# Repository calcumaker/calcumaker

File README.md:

# Calcumaker 16

> Repo: `calcumaker` · Product: **Calcumaker 16** (see [`NAMING.md`](NAMING.md))

A wide-format, full-size **Cherry MX** **programmer's / technical RPN
calculator**. It carries the HP-16C tradition — hexadecimal / octal / binary /
decimal entry, bitwise operators, and selectable word sizes — and extends it far
past what any single Voyager could do, with **arbitrary-precision** math: **GNU
MP** for big integers, **MPFR** for correctly-rounded floating-point and
transcendentals, and **MPC** for complex numbers. The 16C is the grounding
default (a faithful programmer's machine — `√-1` is `Error 0`, just like the
real one); switchable **personalities** (16C / 15C / SCI / FIN) and a SETUP menu
turn on the scientific and complex features on top. The top of the RPN stack is
shown live on a **multi-row 7-segment display** (2–3 rows) that mounts on its
**own angled PCB**. Battery + USB-C powered; a low-power STM32 keeps it alive
between keystrokes.

> Real keyswitches, a real stack you can see, and answers that are correct to as
> many digits as you ask for.

## Features

- **Programmer's RPN core (HP-16C lineage):** HEX/DEC/OCT/BIN modes, bitwise and
  shift/rotate ops, selectable word size, two's-complement / unsigned / one's-
  complement integer modes.
- **Arbitrary precision (single math path — no fallback):**
  - **GNU MP (libgmp)** — unbounded integers (huge hex/decimal, exact bitwise).
  - **MPFR (libmpfr)** — correctly-rounded floating point + transcendentals
    (sin/cos/exp/ln/…) at user-selectable precision.
  - **MPC (libmpc)** — arbitrary-precision **complex numbers** (HP-42S/15C model:
    one stack object, rectangular `a+bi` or polar `r∠θ`, complex-aware functions,
    CPXRES auto-promotion so `√-4 → 2i`). Off on the 16C, on for the scientific
    personalities and toggleable in SETUP.
  - Packaged as the **`calcumaker-core`** library (`no_std`) over our own
    **`gmp-mpfr-nostd`** FFI bindings — host-testable and runnable today
    (`cargo test`, `cargo run --example repl`).
- **Switchable personalities:** **16C** (programmer, the grounding default),
  **15C** (advanced scientific — the one that natively had complex), **SCI**
  (general scientific), **FIN** (HP-12C-style financial) — one keyboard, chosen
  in SETUP, each just a keymap + defaults over the same superset engine.
- **Field updates over USB-C:** flash new firmware with `dfu-util` via the STM32
  ROM DFU bootloader (`make dfu`) — no ST-Link needed; BOOT0 is the backup.
- **Host emulator:** `calcumaker-emu` runs the whole device UI — keymap, f/g
  shifts, digit entry, the multi-row 7-seg display rendered from the real
  TM1640 segment bytes — on a standard terminal (`cargo run`).
- **Visible RPN stack:** multi-row 7-segment display (2–3 rows) shows the top of
  the stack at once.
- **Split design:** the display lives on its **own PCB** that angles upward;
  only power, the display serial bus, and optional aux-display I²C cross the FFC
  to the MCU board — which keeps wiring simple.
- **Full-size Cherry MX keyswitches:** a wide, tactile, technical-use keypad.
- **Battery + USB-C:** 1S Li-ion with USB-C charging + buck-boost rail; aggressive
  sleep between keypresses for long runtime.
- **Rust firmware:** `no_std` main loop on the **STM32U575RGT6** (Cortex-M33,
  1 MB / 768 KB, ULP — see `DESIGN.md`).

## Hardware Stack

Calcumaker 16 is a three-board KiCad 10 design:

- **`calcumaker-mcu`** is the bottom brain/PSU board: STM32U575, USB-C power and
  charging, the 3V3 rail, the gated 5V display rail, SWD, clocking, the display
  FFC connector, and the keyboard mezzanine.
- **`calcumaker-keyboard`** is the top/front-panel board: 49 Cherry MX keys (a 2U ENTER),
  per-key diodes, annunciator LEDs, and a small STM32G0 keyboard scanner that
  reports key events to the U575 instead of routing the raw matrix across the
  stack.
- **`calcumaker-display`** is the angled display board: three repeated 16-digit
  7-segment rows driven by TM1640s, plus the display FFC and optional aux OLED
  socket.

The schematics are generated from per-board manifests under `hardware/scripts/`
and then placed/wired in KiCad. The display board uses a fully wired
multi-channel row sheet; the MCU and keyboard boards carry the generated sheet
structure plus on-canvas wiring notes. See [`hardware/README.md`](hardware/README.md)
and [`DESIGN.md`](DESIGN.md) for the current hardware source of truth.

## Architecture

```
   DISPLAY BOARD (calcumaker-display) — angled, cabled to the MCU board
   ┌──────────────────────────────────────────────────┐
   │  7-segment RPN stack: 3 rows × 16 digits (2–3 on) │
   │   48× FJ5161AH 0.56" single-digit CC (THT)        │
   │   3× TM1640 driver (1 per row, 2-wire bus)        │
   └──────────────────────────────────────────────────┘
       │ 12-position 0.5mm FFC: +5V, GND, CLK + DIN×3
       │ (5V logic) + 3V3/I²C for the aux OLED — cables down to the MCU board
       ╧
   KEYBOARD BOARD (calcumaker-keyboard) — TOP of stack, keys face up
   ┌──────────────────────────────────────────────────┐
   │  full-size Cherry MX key matrix (+ per-key diode) │
   │  STM32G0 scanner + annunciator LEDs (f g C G lo-b)│
   └──────────────────────┬┬──────────────────────────┘
     low-profile Hirose DF40 mezzanine (0.4mm, 1.5mm stack) + standoffs
        ││  I²C + UART + KB_IRQ (wake) + 3V3/GND  (matrix stays on the G0)
   MCU BOARD (calcumaker-mcu) — BOTTOM of stack
   ┌──────────────────────┴┴──────────────────────────┐
   │  EN-gated 5V boost ──► display │ 74HCT125 (3V3→5V)│
   │   ┌───────────────────────────────────────────┐   │  USB-C ── console /
   │   │ STM32U575RGT6 (Cortex-M33, 1MB/768KB, ULP) │   │          provisioning
   │   │  Rust no_std main loop (embassy)           │   │
   │   │   calcumaker-core: RPN engine              │   │
   │   │        └ GMP + MPFR  (single path)         │   │
   │   │   heap: embedded-alloc (TLSF)              │   │
   │   └────────────────────────────────────────────┘   │
   └───────┬───────────────────────────────────────────┘
           │ VSYS
   1S Li-ion ── USB-C charger ── load-share ── VSYS ──┬── buck-boost → 3V3 (MCU, ULP)
                                                      └── 5V boost (EN-gated) → display
```

## Firmware Stack

The firmware is deliberately split so there is one calculator and multiple thin
I/O bindings around it:

```
   host terminal                         STM32U575 firmware
   ┌─────────────────────┐               ┌─────────────────────┐
   │ calcumaker-emu      │               │ calcumaker-fw       │
   │ crossterm UI        │               │ no_std / embassy    │
   │ host keys + ASCII   │               │ keyboard link +     │
   │ 7-seg rendering     │               │ TM1640 bus + heap   │
   └──────────┬──────────┘               └──────────┬──────────┘
              │                                     │
              └──────────────┬──────────────────────┘
                             │
                    ┌────────▼────────┐
                    │ calcumaker-core │
                    │ Calc + App +    │
                    │ keys + seg7     │
                    └────────┬────────┘
                             │
                    ┌────────▼────────┐
                    │ gmp-mpfr-nostd  │
                    │ Integer + Float │
                    └────────┬────────┘
                             │
          host system GMP/MPFR or target cross-built GMP/MPFR
```

- **`gmp-mpfr-nostd`** is the math FFI layer: `no_std` + `alloc` wrappers for
  GMP integers and MPFR floats. On the host it links system/Homebrew GMP+MPFR;
  on the MCU it links the cross-built static libraries.
- **`calcumaker-core`** is the calculator: RPN stack, exact integer/programmer
  operations, MPFR real math, modes, keymap and f/g shift layers, entry editing,
  errors, and TM1640 7-segment byte generation. This crate is the single numeric
  path: no `rug`, no `std`, no pure-Rust fallback.
- **`calcumaker-emu`** runs the same `App` on a desktop terminal. It maps host
  keys to the physical matrix and renders the real segment bytes as 7-segment
  art, so scripted examples exercise the same key handling and display pipeline
  the device uses.
- **`calcumaker-fw`** is the U575 board binding: heap setup, power/display
  bring-up, keyboard event intake, and the TM1640 bus. The keyboard board's G0
  firmware owns matrix scan, debounce, wake/IRQ, and annunciator drive; the U575
  consumes `(row,col)` key events and feeds them to `calcumaker_core::App`.

Useful firmware entry points:

```sh
cd firmware/calcumaker-core
cargo test
cargo run --example repl

cd ../calcumaker-emu
cargo run
cargo run -- --press "2;3+"

cd ../..
firmware/scripts/build-gmp-mpfr-arm.sh
```

Host engine tests, the token REPL, and the terminal emulator work today against
the real GMP/MPFR libraries. The target GMP/MPFR build is cross-built and
link-verified; remaining firmware work is MCU/HAL bring-up, newlib/libm link
cleanup, heap routing for GMP allocations, and the keyboard-G0 firmware.

## Repository Structure

```
calcumaker/
├── hardware/                     # PCB design (KiCad 10) — split, three boards
│   ├── lib/                      # project-specific symbols/footprints/3D (shared)
│   │   ├── symbols/ footprints.pretty/ 3dmodels/
│   ├── calcumaker-mcu/           # MCU board (brain/PSU): MCU + PSU + clock + SWD + display-IF + keyboard mezzanine
│   │   ├── calcumaker-mcu.kicad_pro
│   │   ├── (root + mcu / clock / prog / psu / display_if / keyboard_if sub-sheets — generated)
│   │   ├── sym-lib-table · fp-lib-table
│   ├── calcumaker-keyboard/      # keyboard board (stacks above MCU): Cherry MX matrix + annunciators + MCU mezzanine
│   │   ├── calcumaker-keyboard.kicad_pro
│   │   ├── (root + keypad / annunc / main_if sub-sheets — generated)
│   │   ├── sym-lib-table · fp-lib-table
│   ├── calcumaker-display/       # display board (angled, cabled): 7-seg stack + driver + interconnect
│   │   ├── calcumaker-display.kicad_pro
│   │   ├── (root + display_row ×3 / interconnect / aux sub-sheets — generated)
│   │   ├── sym-lib-table · fp-lib-table
│   ├── scripts/                  # schgen engine + per-board manifests, check/render, JLCPCB
│   ├── Makefile                  # PROJECTS = calcumaker-mcu calcumaker-keyboard calcumaker-display
│   ├── LICENSE                   # CERN-OHL-S v2 (hardware)
│   ├── README.md
│   ├── sym-lib-table
│   └── fp-lib-table
├── firmware/
│   ├── gmp-mpfr-nostd/           # own no_std FFI to GMP/MPFR ("rug, but no_std")
│   ├── calcumaker-core/          # the CALCULATOR: engine + keymap + App + 7-seg
│   │   ├── src/                  #   lib, calc, value, format, keys, app, seg7
│   │   ├── tests/ · examples/repl.rs
│   │   └── Cargo.toml            #   single math path (no fallback)
│   ├── calcumaker-emu/           # HOST EMULATOR: the same App on a terminal
│   ├── calcumaker-fw/            # Rust no_std board binary (STM32U575 / embassy)
│   │   ├── Cargo.toml · .cargo/config.toml
│   │   ├── memory.x · build.rs · rust-toolchain.toml
│   │   └── src/                  #   main, keyboard input/link, display (TM1640 bus)
│   ├── scripts/                  # build-gmp-mpfr-arm.sh (cross-build for thumbv8m)
│   ├── common/                   # shared HAL/utilities
│   └── shared/                   # shared protocol/definitions
├── reference/                    # datasheets + dependency pointers
├── DESIGN.md                     # full hardware/firmware design + open questions
├── NAMING.md                     # product naming (Calcumaker 16)
└── LICENSE                       # AGPL-3.0 (firmware)
```

## Key Components

| Component | Part | Status |
|-----------|------|--------|
| MCU | STM32U575RGT6 (1MB/768KB, M33, ULP, LQFP-64) | ✅ selected — LCSC C5270980, JLCPCB Extended |
| Display | 3 rows × 16 digits: 3× TM1640 + 48× FJ5161AH 0.56" CC (THT) | ✅ LCSC C5337152 / C8093 |
| Keys | 5×10 grid, 49 full-size Cherry MX (2U double-height ENTER) + keyboard STM32G0 scanner | electrical/keymap decided; physical layout details still TBD |
| Display interconnect | 12-position 0.5mm FFC: +5V/GND, CLK + DIN×3, 3V3/I²C aux lines | selected in `DESIGN.md`; verify cable length/orientation at layout |
| Power | 1S Li-ion + USB-C charge; **3V3 (TPS63900, MCU)** + **EN-gated 5V boost (display)** | 3V3 ✅; 5V boost + 74HCT125 level shifter TBD (research) |
| Math | GNU MP + MPFR via `calcumaker-core` + own `gmp-mpfr-nostd` (single path) | ✅ no_std, host-tested + REPL + emulator; cross-built + link-verified for the target |

## Status

**The calculator works on the host today**: engine + keymap + display pipeline
are host-tested, and `calcumaker-emu` runs the full device UI on a terminal.
GMP/MPFR are cross-built + link-verified for the STM32 target. **MCU, keypad
layout (5×10), software stack, display BOM, and power architecture are decided** (see
`DESIGN.md` / `hardware/PARTS.md`). The three-board hardware split is in the
repo; the display board is fully wired as a multi-channel KiCad design, while
the MCU and keyboard boards generate from their manifests and still need
eeschema wiring/layout work. Remaining firmware work: U575 MCU bring-up
(embassy + newlib/libm link + heap routing) and the keyboard-G0 scanner
firmware. Battery sizing and fabrication are still ahead.

## License

- **Firmware:** [AGPL-3.0](LICENSE) (compatible with the LGPLv3 GMP/MPFR).
- **Hardware:** [CERN-OHL-S v2](hardware/LICENSE) (strongly reciprocal — matches
  the AGPL copyleft posture).

Copyright (c) 2026 calcumaker authors.

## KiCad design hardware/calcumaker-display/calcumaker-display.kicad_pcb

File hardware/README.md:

# Calcumaker 16 — hardware

KiCad 10 design for the **Calcumaker 16** programmer's / technical RPN
calculator. **Split design** — two stacked PCBs and one of two cabled display variants:

- **`calcumaker-mcu/`** — the brain/PSU board: MCU (STM32U575RGT6), PSU (USB-C
  charge + buck-boost), clock, SWD, the display interconnect (its 5V rail and
  level shifter live on the display module), and a mezzanine to the keyboard. *Bottom of
  the stack.*
- **`calcumaker-keyboard/`** — the front-panel board: the 49-key Cherry MX matrix (2U ENTER)
  + per-key diodes + the annunciator LEDs + the mating mezzanine header.
  *Mezzanine-stacks directly above the MCU board* (keeps a dense LQFP-64 off the
  through-hole key matrix).
- **`calcumaker-display/`** — the multi-row 7-segment RPN stack (2–3 rows) + its
  driver ICs + the interconnect back to the MCU board. Mounts at an upward angle,
  cabled; power, the display serial bus, and optional aux-display I2C cross the
  FFC.
- **`calcumaker-matrix/`** — alternative 96 × 24 addressable-pixel display with
  RP2040 control, USB programming and a dedicated LED power inlet.

See `../DESIGN.md` for the full design and `scripts/README.md` for the
schematic-generation flow. Build docs/BOMs/fab packages with the `Makefile`
(`make help`).

The MCU and keyboard schematics are wired and verified with KiCad 10.0.6.
Run `make check-wiring` for electrical net assertions and ERC validation.
See [WIRING_REVIEW.md](WIRING_REVIEW.md) for the pin maps, reviewed ERC warning,
power corrections, and remaining physical validation. Edit the schematics
directly; forcing the older placement manifests would discard this wiring.

The MCU board also has a [provisional PCB floor plan](calcumaker-mcu/FLOORPLAN.md):
75 placed components in functional groups, local supply bypasses, and a 70 × 50 mm
outline for the cabled configuration. It is unrouted; the placement review records
the remaining mechanical and fabrication-rule decisions.

The keyboard has a [PCB and mechanical plate floor plan](calcumaker-keyboard/FLOORPLAN.md)
with 49 key-cell groups, local RGB bypasses, a centered vertical 2U ENTER and
dedicated `Plate.Cuts`, `Keycaps` and mechanical annotation layers. Run
`make keyboard-plate` to export the separate plate DXF and reference SVG.

Both display variants have grouped, unrouted floor plans:
[48-digit seven-segment](calcumaker-display/FLOORPLAN.md) and
[2,304-pixel matrix](calcumaker-matrix/FLOORPLAN.md). They include local bypasses,
mechanical viewing references and position CSVs. Run `make check-display-wiring`
to check every digit/pixel net and ERC, and `make display-mechanical` to export
window DXFs and reference SVGs. These are provisional mechanical envelopes;
the matrix power path and both boards' remaining part choices require qualification.
All four boards' edited schematics are authoritative over the older manifests.

## Library

`lib/{symbols,footprints.pretty,3dmodels}` holds project-specific parts (shared
by all boards, lib name `calcumaker`); most parts resolve to KiCad bundled
libraries.

## License — Hardware: CERN-OHL-S v2

The hardware (schematics, PCB layouts, and associated design files under
`hardware/`) is licensed under the **CERN Open Hardware Licence Version 2 —
Strongly Reciprocal** (`CERN-OHL-S-2.0`). Full text: [`LICENSE`](LICENSE).
Chosen to match the strong-copyleft posture of the AGPL-3.0 firmware.

**Third-party library parts** (vendored symbols / footprints / 3D models) carry their
own upstream licenses — CERN-OHL-P, MIT, and CC-BY-SA-4.0-with-exception — all of which
are compatible with incorporation into a CERN-OHL-S v2 design. Every one is indexed,
with its source and license, in **[`lib/ATTRIBUTIONS.md`](lib/ATTRIBUTIONS.md)**.

> Copyright (c) 2026 calcumaker authors.
>
> This source describes Open Hardware and is licensed under the CERN-OHL-S v2.
>
> You may redistribute and modify this source and make products using it under
> the terms of the CERN-OHL-S v2 (https://ohwr.org/cern_ohl_s_v2.txt).
>
> This source is distributed WITHOUT ANY EXPRESS OR IMPLIED WARRANTY, INCLUDING
> OF MERCHANTABILITY, SATISFACTORY QUALITY AND FITNESS FOR A PARTICULAR PURPOSE.
> Please see the CERN-OHL-S v2 for applicable conditions.
>
> Source location: https://github.com/calcumaker/calcumaker
>
> As per CERN-OHL-S v2 § 4, if you produce a device using this source, you
> should where practicable keep the above Source Location visible on the device.

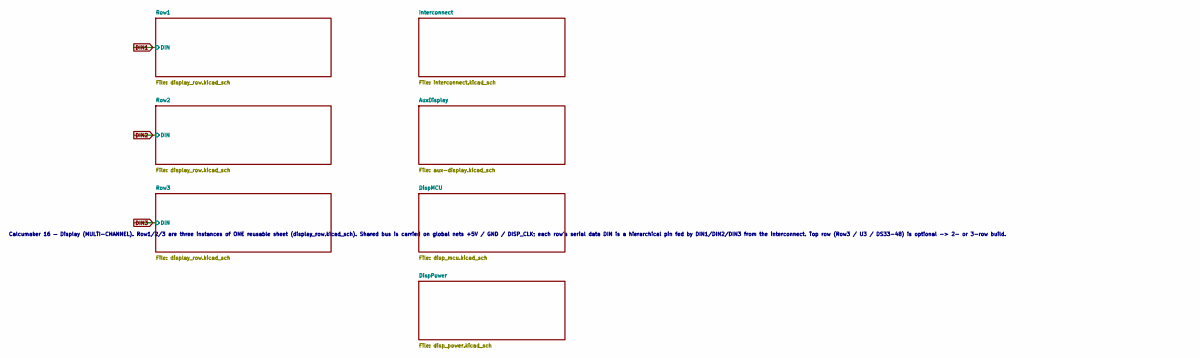
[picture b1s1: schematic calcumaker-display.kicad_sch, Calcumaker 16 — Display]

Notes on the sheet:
Calcumaker 16 — Display (MULTI-CHANNEL). Row1/2/3 are three instances of ONE reusable sheet (display_row.kicad_sch). Shared bus is carried on global nets +5V / GND / DISP_CLK; each row's serial data DIN is a hierarchical pin fed by DIN1/DIN2/DIN3 from the interconnect. Top row (Row3 / U3 / DS33-48)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

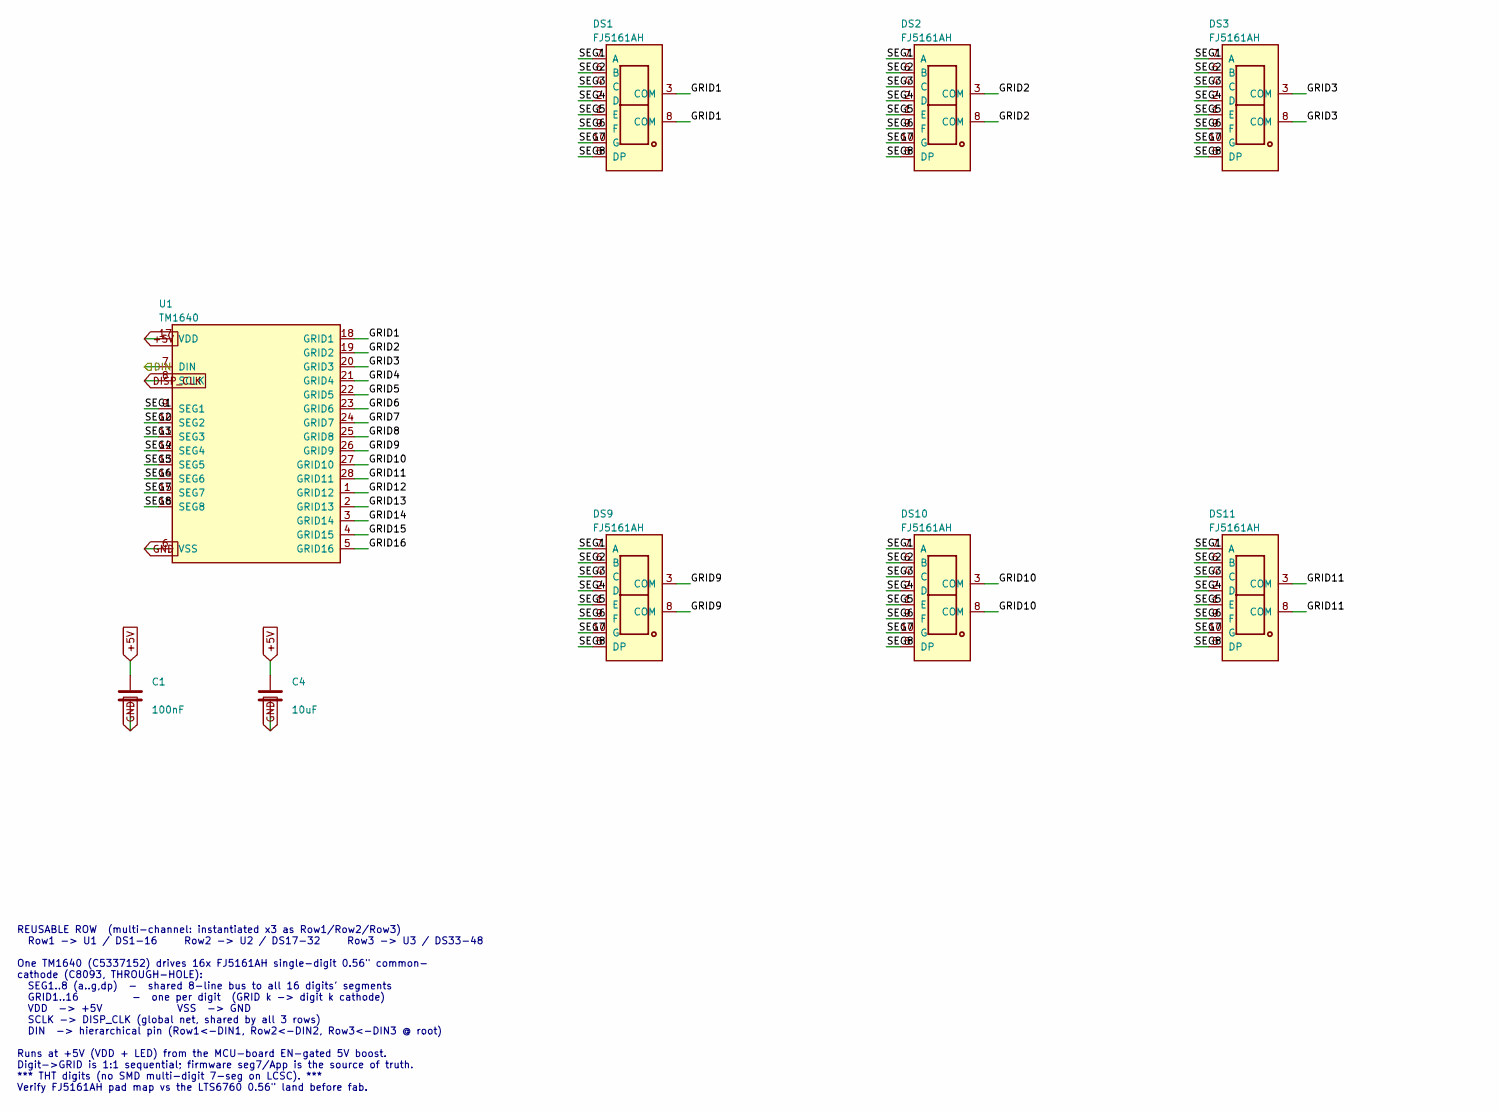
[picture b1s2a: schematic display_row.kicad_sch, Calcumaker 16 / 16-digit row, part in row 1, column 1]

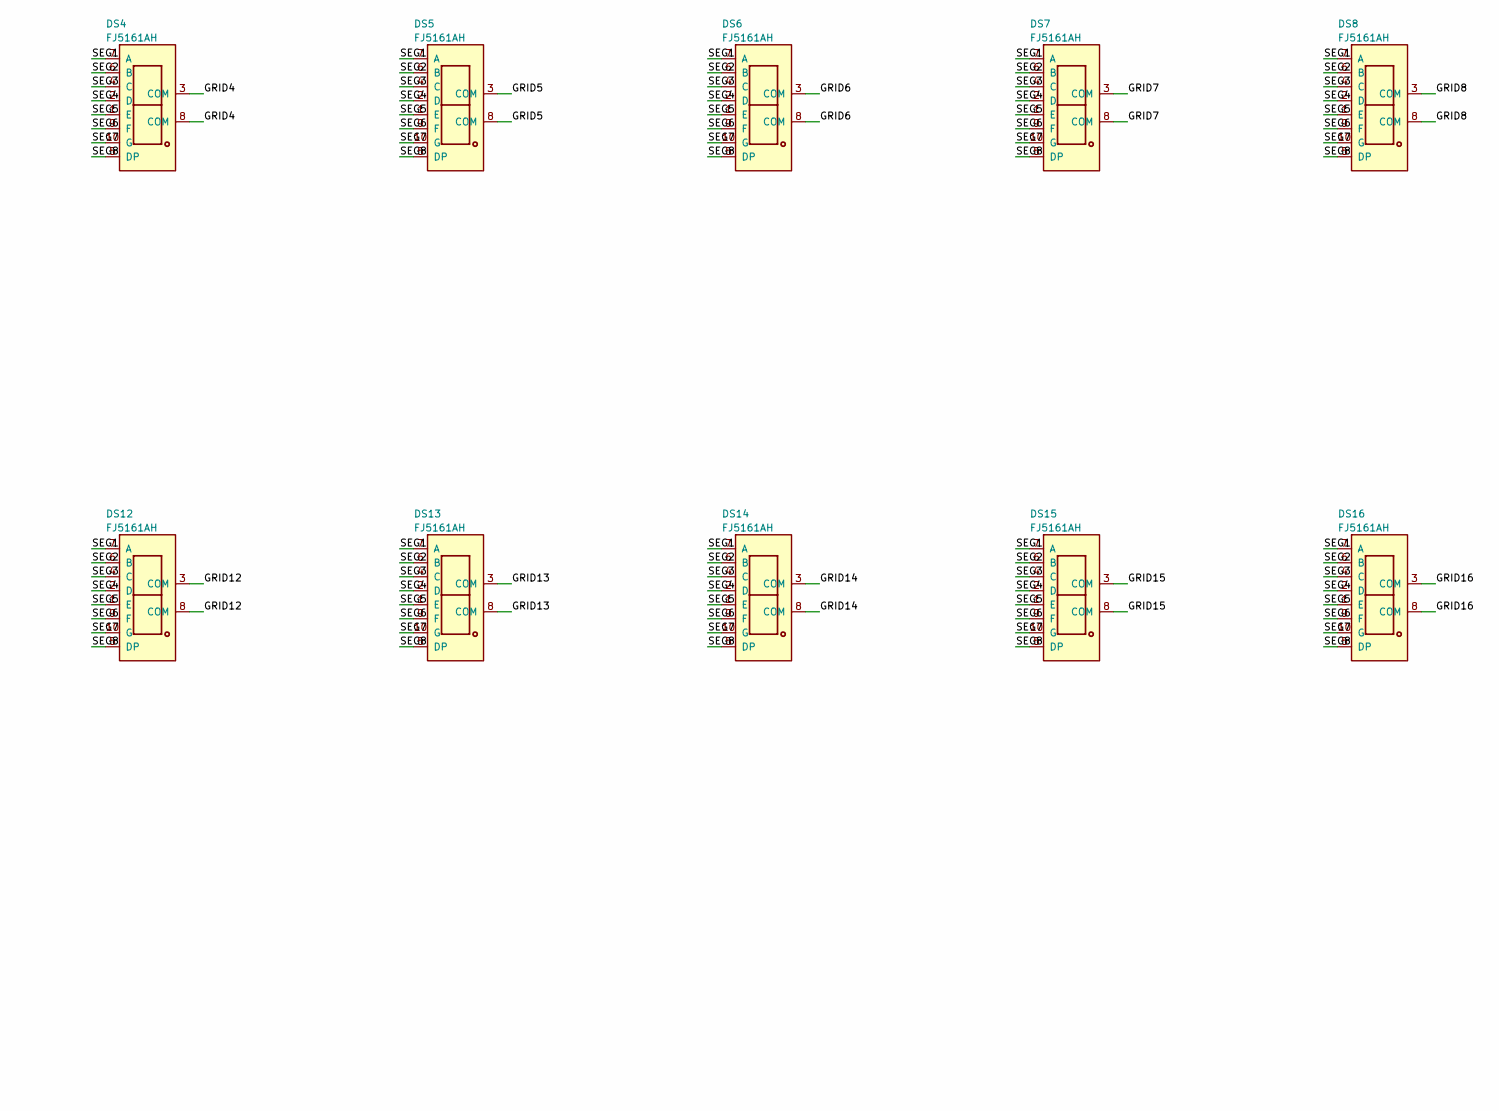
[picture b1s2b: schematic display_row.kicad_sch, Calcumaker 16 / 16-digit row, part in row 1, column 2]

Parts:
C1: 100nF; C_0402_1005Metric; LCSC C1525
C4: 10uF; C_0603_1608Metric; LCSC C15850
DS1, DS2, DS3, DS4, DS5, DS6, DS7, DS8, DS9, DS10, DS11, DS12, DS13, DS14, DS15, DS16: FJ5161AH; 7SegmentLED_LTS6760_LTS6780; MPN FJ5161AH; LCSC C8093
U1: TM1640; SOIC-28W_7.5x18.7mm_P1.27mm; MPN TM1640; LCSC C5337152

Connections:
+5V: C1.1, C4.1, U1.17 (VDD); also elsewhere on the board
/Row1/GRID1: DS1.3 (COM), DS1.8 (COM), U1.18 (GRID1)
/Row1/GRID2: DS2.3 (COM), DS2.8 (COM), U1.19 (GRID2)
/Row1/GRID3: DS3.3 (COM), DS3.8 (COM), U1.20 (GRID3)
/Row1/GRID4: DS4.3 (COM), DS4.8 (COM), U1.21 (GRID4)
/Row1/GRID5: DS5.3 (COM), DS5.8 (COM), U1.22 (GRID5)
/Row1/GRID6: DS6.3 (COM), DS6.8 (COM), U1.23 (GRID6)
/Row1/GRID7: DS7.3 (COM), DS7.8 (COM), U1.24 (GRID7)
/Row1/GRID8: DS8.3 (COM), DS8.8 (COM), U1.25 (GRID8)
/Row1/GRID9: DS9.3 (COM), DS9.8 (COM), U1.26 (GRID9)
/Row1/GRID10: DS10.3 (COM), DS10.8 (COM), U1.27 (GRID10)
/Row1/GRID11: DS11.3 (COM), DS11.8 (COM), U1.28 (GRID11)
/Row1/GRID12: DS12.3 (COM), DS12.8 (COM), U1.1 (GRID12)
/Row1/GRID13: DS13.3 (COM), DS13.8 (COM), U1.2 (GRID13)
/Row1/GRID14: DS14.3 (COM), DS14.8 (COM), U1.3 (GRID14)
/Row1/GRID15: DS15.3 (COM), DS15.8 (COM), U1.4 (GRID15)
/Row1/GRID16: DS16.3 (COM), DS16.8 (COM), U1.5 (GRID16)
/Row1/SEG1: DS1.7 (A), DS2.7 (A), DS3.7 (A), DS4.7 (A), DS5.7 (A), DS6.7 (A), DS7.7 (A), DS8.7 (A), DS9.7 (A), DS10.7 (A), DS11.7 (A), DS12.7 (A), DS13.7 (A), DS14.7 (A), DS15.7 (A), DS16.7 (A), U1.9 (SEG1)
/Row1/SEG2: DS1.6 (B), DS2.6 (B), DS3.6 (B), DS4.6 (B), DS5.6 (B), DS6.6 (B), DS7.6 (B), DS8.6 (B), DS9.6 (B), DS10.6 (B), DS11.6 (B), DS12.6 (B), DS13.6 (B), DS14.6 (B), DS15.6 (B), DS16.6 (B), U1.10 (SEG2)
/Row1/SEG3: DS1.4 (C), DS2.4 (C), DS3.4 (C), DS4.4 (C), DS5.4 (C), DS6.4 (C), DS7.4 (C), DS8.4 (C), DS9.4 (C), DS10.4 (C), DS11.4 (C), DS12.4 (C), DS13.4 (C), DS14.4 (C), DS15.4 (C), DS16.4 (C), U1.11 (SEG3)
/Row1/SEG4: DS1.2 (D), DS2.2 (D), DS3.2 (D), DS4.2 (D), DS5.2 (D), DS6.2 (D), DS7.2 (D), DS8.2 (D), DS9.2 (D), DS10.2 (D), DS11.2 (D), DS12.2 (D), DS13.2 (D), DS14.2 (D), DS15.2 (D), DS16.2 (D), U1.12 (SEG4)
/Row1/SEG5: DS1.1 (E), DS2.1 (E), DS3.1 (E), DS4.1 (E), DS5.1 (E), DS6.1 (E), DS7.1 (E), DS8.1 (E), DS9.1 (E), DS10.1 (E), DS11.1 (E), DS12.1 (E), DS13.1 (E), DS14.1 (E), DS15.1 (E), DS16.1 (E), U1.13 (SEG5)
/Row1/SEG6: DS1.9 (F), DS2.9 (F), DS3.9 (F), DS4.9 (F), DS5.9 (F), DS6.9 (F), DS7.9 (F), DS8.9 (F), DS9.9 (F), DS10.9 (F), DS11.9 (F), DS12.9 (F), DS13.9 (F), DS14.9 (F), DS15.9 (F), DS16.9 (F), U1.14 (SEG6)
/Row1/SEG7: DS1.10 (G), DS2.10 (G), DS3.10 (G), DS4.10 (G), DS5.10 (G), DS6.10 (G), DS7.10 (G), DS8.10 (G), DS9.10 (G), DS10.10 (G), DS11.10 (G), DS12.10 (G), DS13.10 (G), DS14.10 (G), DS15.10 (G), DS16.10 (G), U1.15 (SEG7)
/Row1/SEG8: DS1.5 (DP), DS2.5 (DP), DS3.5 (DP), DS4.5 (DP), DS5.5 (DP), DS6.5 (DP), DS7.5 (DP), DS8.5 (DP), DS9.5 (DP), DS10.5 (DP), DS11.5 (DP), DS12.5 (DP), DS13.5 (DP), DS14.5 (DP), DS15.5 (DP), DS16.5 (DP), U1.16 (SEG8)
DIN1: U1.7 (DIN); also elsewhere on the board
DISP_CLK: U1.8 (SCLK); also elsewhere on the board
GND: C1.2, C4.2, U1.6 (VSS); also elsewhere on the board

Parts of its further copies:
C2, C3: 100nF; C_0402_1005Metric; LCSC C1525
C5, C6: 10uF; C_0603_1608Metric; LCSC C15850
DS17, DS18, DS19, DS20, DS21, DS22, DS23, DS24, DS25, DS26, DS27, DS28, DS29, DS30, DS31, DS32, DS33, DS34, DS35, DS36, DS37, DS38, DS39, DS40, DS41, DS42, DS43, DS44, DS45, DS46, DS47, DS48: FJ5161AH; 7SegmentLED_LTS6760_LTS6780; MPN FJ5161AH; LCSC C8093
U2, U3: TM1640; SOIC-28W_7.5x18.7mm_P1.27mm; MPN TM1640; LCSC C5337152

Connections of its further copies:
+5V: C2.1, C3.1, C5.1, C6.1, U2.17 (VDD), U3.17 (VDD); also elsewhere on the board
/Row2/GRID1: DS17.3 (COM), DS17.8 (COM), U2.18 (GRID1)
/Row2/GRID2: DS18.3 (COM), DS18.8 (COM), U2.19 (GRID2)
/Row2/GRID3: DS19.3 (COM), DS19.8 (COM), U2.20 (GRID3)
/Row2/GRID4: DS20.3 (COM), DS20.8 (COM), U2.21 (GRID4)
/Row2/GRID5: DS21.3 (COM), DS21.8 (COM), U2.22 (GRID5)
/Row2/GRID6: DS22.3 (COM), DS22.8 (COM), U2.23 (GRID6)
/Row2/GRID7: DS23.3 (COM), DS23.8 (COM), U2.24 (GRID7)
/Row2/GRID8: DS24.3 (COM), DS24.8 (COM), U2.25 (GRID8)
/Row2/GRID9: DS25.3 (COM), DS25.8 (COM), U2.26 (GRID9)
/Row2/GRID10: DS26.3 (COM), DS26.8 (COM), U2.27 (GRID10)
/Row2/GRID11: DS27.3 (COM), DS27.8 (COM), U2.28 (GRID11)
/Row2/GRID12: DS28.3 (COM), DS28.8 (COM), U2.1 (GRID12)
/Row2/GRID13: DS29.3 (COM), DS29.8 (COM), U2.2 (GRID13)
/Row2/GRID14: DS30.3 (COM), DS30.8 (COM), U2.3 (GRID14)
/Row2/GRID15: DS31.3 (COM), DS31.8 (COM), U2.4 (GRID15)
/Row2/GRID16: DS32.3 (COM), DS32.8 (COM), U2.5 (GRID16)
/Row2/SEG1: DS17.7 (A), DS18.7 (A), DS19.7 (A), DS20.7 (A), DS21.7 (A), DS22.7 (A), DS23.7 (A), DS24.7 (A), DS25.7 (A), DS26.7 (A), DS27.7 (A), DS28.7 (A), DS29.7 (A), DS30.7 (A), DS31.7 (A), DS32.7 (A), U2.9 (SEG1)
/Row2/SEG2: DS17.6 (B), DS18.6 (B), DS19.6 (B), DS20.6 (B), DS21.6 (B), DS22.6 (B), DS23.6 (B), DS24.6 (B), DS25.6 (B), DS26.6 (B), DS27.6 (B), DS28.6 (B), DS29.6 (B), DS30.6 (B), DS31.6 (B), DS32.6 (B), U2.10 (SEG2)
/Row2/SEG3: DS17.4 (C), DS18.4 (C), DS19.4 (C), DS20.4 (C), DS21.4 (C), DS22.4 (C), DS23.4 (C), DS24.4 (C), DS25.4 (C), DS26.4 (C), DS27.4 (C), DS28.4 (C), DS29.4 (C), DS30.4 (C), DS31.4 (C), DS32.4 (C), U2.11 (SEG3)
/Row2/SEG4: DS17.2 (D), DS18.2 (D), DS19.2 (D), DS20.2 (D), DS21.2 (D), DS22.2 (D), DS23.2 (D), DS24.2 (D), DS25.2 (D), DS26.2 (D), DS27.2 (D), DS28.2 (D), DS29.2 (D), DS30.2 (D), DS31.2 (D), DS32.2 (D), U2.12 (SEG4)
/Row2/SEG5: DS17.1 (E), DS18.1 (E), DS19.1 (E), DS20.1 (E), DS21.1 (E), DS22.1 (E), DS23.1 (E), DS24.1 (E), DS25.1 (E), DS26.1 (E), DS27.1 (E), DS28.1 (E), DS29.1 (E), DS30.1 (E), DS31.1 (E), DS32.1 (E), U2.13 (SEG5)
/Row2/SEG6: DS17.9 (F), DS18.9 (F), DS19.9 (F), DS20.9 (F), DS21.9 (F), DS22.9 (F), DS23.9 (F), DS24.9 (F), DS25.9 (F), DS26.9 (F), DS27.9 (F), DS28.9 (F), DS29.9 (F), DS30.9 (F), DS31.9 (F), DS32.9 (F), U2.14 (SEG6)
/Row2/SEG7: DS17.10 (G), DS18.10 (G), DS19.10 (G), DS20.10 (G), DS21.10 (G), DS22.10 (G), DS23.10 (G), DS24.10 (G), DS25.10 (G), DS26.10 (G), DS27.10 (G), DS28.10 (G), DS29.10 (G), DS30.10 (G), DS31.10 (G), DS32.10 (G), U2.15 (SEG7)
/Row2/SEG8: DS17.5 (DP), DS18.5 (DP), DS19.5 (DP), DS20.5 (DP), DS21.5 (DP), DS22.5 (DP), DS23.5 (DP), DS24.5 (DP), DS25.5 (DP), DS26.5 (DP), DS27.5 (DP), DS28.5 (DP), DS29.5 (DP), DS30.5 (DP), DS31.5 (DP), DS32.5 (DP), U2.16 (SEG8)
/Row3/GRID1: DS33.3 (COM), DS33.8 (COM), U3.18 (GRID1)
/Row3/GRID2: DS34.3 (COM), DS34.8 (COM), U3.19 (GRID2)
/Row3/GRID3: DS35.3 (COM), DS35.8 (COM), U3.20 (GRID3)
/Row3/GRID4: DS36.3 (COM), DS36.8 (COM), U3.21 (GRID4)
/Row3/GRID5: DS37.3 (COM), DS37.8 (COM), U3.22 (GRID5)
/Row3/GRID6: DS38.3 (COM), DS38.8 (COM), U3.23 (GRID6)
/Row3/GRID7: DS39.3 (COM), DS39.8 (COM), U3.24 (GRID7)
/Row3/GRID8: DS40.3 (COM), DS40.8 (COM), U3.25 (GRID8)
/Row3/GRID9: DS41.3 (COM), DS41.8 (COM), U3.26 (GRID9)
/Row3/GRID10: DS42.3 (COM), DS42.8 (COM), U3.27 (GRID10)
/Row3/GRID11: DS43.3 (COM), DS43.8 (COM), U3.28 (GRID11)
/Row3/GRID12: DS44.3 (COM), DS44.8 (COM), U3.1 (GRID12)
/Row3/GRID13: DS45.3 (COM), DS45.8 (COM), U3.2 (GRID13)
/Row3/GRID14: DS46.3 (COM), DS46.8 (COM), U3.3 (GRID14)
/Row3/GRID15: DS47.3 (COM), DS47.8 (COM), U3.4 (GRID15)
/Row3/GRID16: DS48.3 (COM), DS48.8 (COM), U3.5 (GRID16)
/Row3/SEG1: DS33.7 (A), DS34.7 (A), DS35.7 (A), DS36.7 (A), DS37.7 (A), DS38.7 (A), DS39.7 (A), DS40.7 (A), DS41.7 (A), DS42.7 (A), DS43.7 (A), DS44.7 (A), DS45.7 (A), DS46.7 (A), DS47.7 (A), DS48.7 (A), U3.9 (SEG1)
/Row3/SEG2: DS33.6 (B), DS34.6 (B), DS35.6 (B), DS36.6 (B), DS37.6 (B), DS38.6 (B), DS39.6 (B), DS40.6 (B), DS41.6 (B), DS42.6 (B), DS43.6 (B), DS44.6 (B), DS45.6 (B), DS46.6 (B), DS47.6 (B), DS48.6 (B), U3.10 (SEG2)
/Row3/SEG3: DS33.4 (C), DS34.4 (C), DS35.4 (C), DS36.4 (C), DS37.4 (C), DS38.4 (C), DS39.4 (C), DS40.4 (C), DS41.4 (C), DS42.4 (C), DS43.4 (C), DS44.4 (C), DS45.4 (C), DS46.4 (C), DS47.4 (C), DS48.4 (C), U3.11 (SEG3)
/Row3/SEG4: DS33.2 (D), DS34.2 (D), DS35.2 (D), DS36.2 (D), DS37.2 (D), DS38.2 (D), DS39.2 (D), DS40.2 (D), DS41.2 (D), DS42.2 (D), DS43.2 (D), DS44.2 (D), DS45.2 (D), DS46.2 (D), DS47.2 (D), DS48.2 (D), U3.12 (SEG4)
/Row3/SEG5: DS33.1 (E), DS34.1 (E), DS35.1 (E), DS36.1 (E), DS37.1 (E), DS38.1 (E), DS39.1 (E), DS40.1 (E), DS41.1 (E), DS42.1 (E), DS43.1 (E), DS44.1 (E), DS45.1 (E), DS46.1 (E), DS47.1 (E), DS48.1 (E), U3.13 (SEG5)
/Row3/SEG6: DS33.9 (F), DS34.9 (F), DS35.9 (F), DS36.9 (F), DS37.9 (F), DS38.9 (F), DS39.9 (F), DS40.9 (F), DS41.9 (F), DS42.9 (F), DS43.9 (F), DS44.9 (F), DS45.9 (F), DS46.9 (F), DS47.9 (F), DS48.9 (F), U3.14 (SEG6)
/Row3/SEG7: DS33.10 (G), DS34.10 (G), DS35.10 (G), DS36.10 (G), DS37.10 (G), DS38.10 (G), DS39.10 (G), DS40.10 (G), DS41.10 (G), DS42.10 (G), DS43.10 (G), DS44.10 (G), DS45.10 (G), DS46.10 (G), DS47.10 (G), DS48.10 (G), U3.15 (SEG7)
/Row3/SEG8: DS33.5 (DP), DS34.5 (DP), DS35.5 (DP), DS36.5 (DP), DS37.5 (DP), DS38.5 (DP), DS39.5 (DP), DS40.5 (DP), DS41.5 (DP), DS42.5 (DP), DS43.5 (DP), DS44.5 (DP), DS45.5 (DP), DS46.5 (DP), DS47.5 (DP), DS48.5 (DP), U3.16 (SEG8)
DIN2: U2.7 (DIN); also elsewhere on the board
DIN3: U3.7 (DIN); also elsewhere on the board
DISP_CLK: U2.8 (SCLK), U3.8 (SCLK); also elsewhere on the board
GND: C2.2, C3.2, C5.2, C6.2, U2.6 (VSS), U3.6 (VSS); also elsewhere on the board

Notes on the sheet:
REUSABLE ROW (multi-channel: instantiated x3 as Row1/Row2/Row3) Row1 -> U1 / DS1-16 Row2 -> U2 / DS17-32 Row3 -> U3 / DS33-48 One TM1640 (C5337152) drives 16x FJ5161AH single-digit 0.56" common- cathode (C8093, THROUGH-HOLE): SEG1..8 (a..g,dp) - shared 8-line bus to all 16 digits' segments GRID1..1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

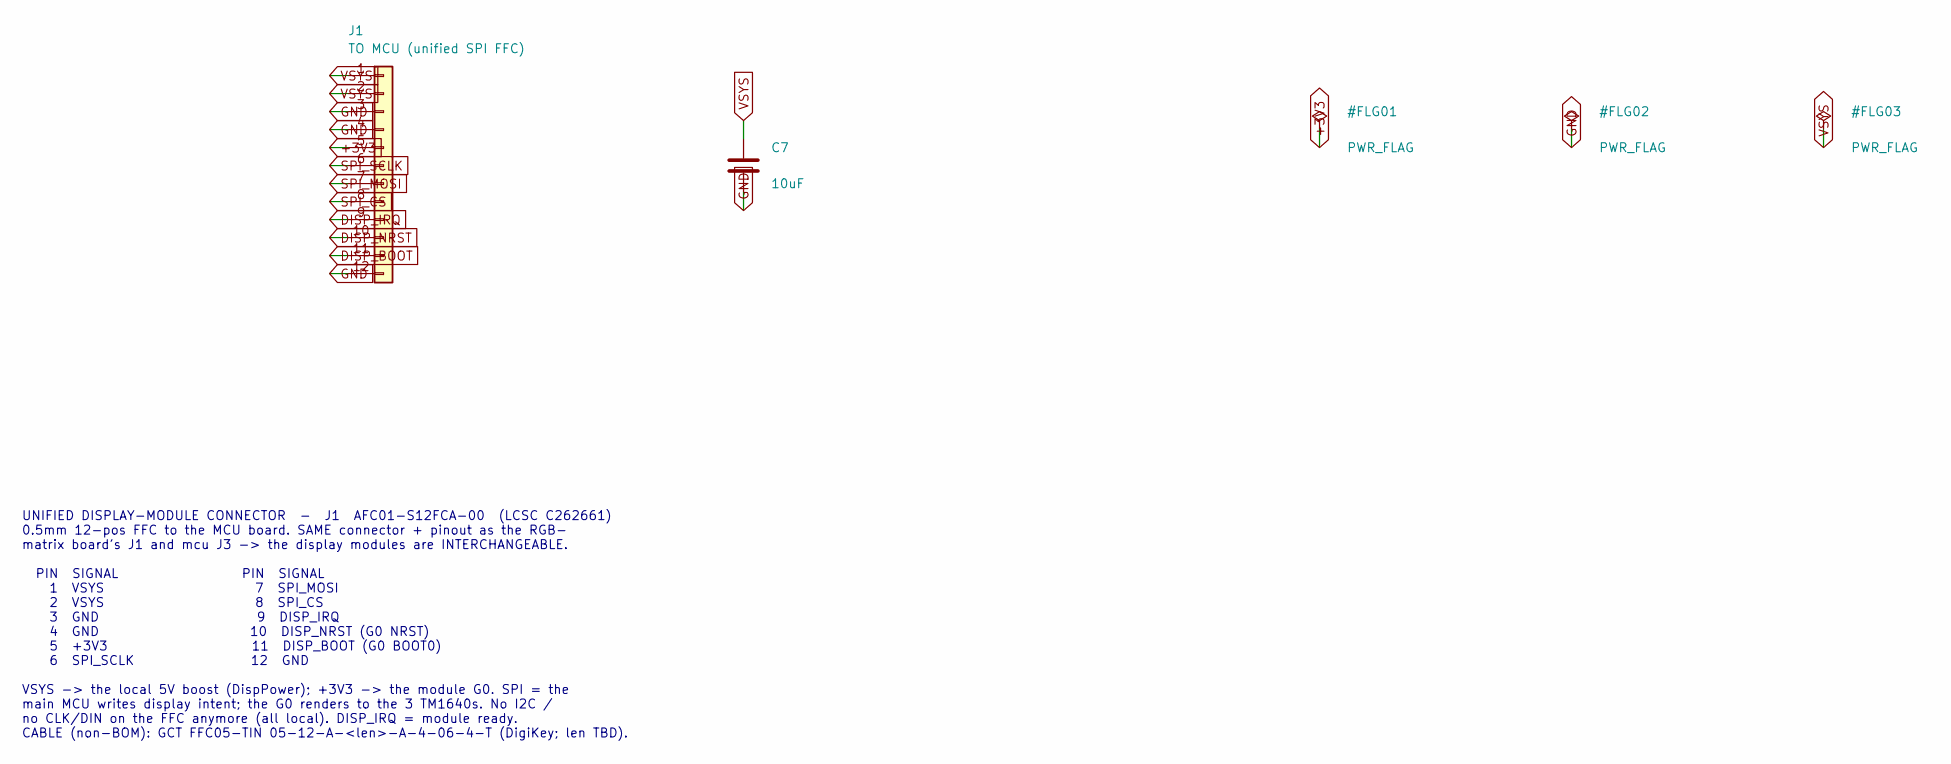
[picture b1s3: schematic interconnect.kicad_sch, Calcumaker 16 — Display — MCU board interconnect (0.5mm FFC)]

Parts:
C7: 10uF; C_0603_1608Metric; LCSC C15850
J1: TO MCU (unified SPI FFC); Hirose_FH12-12S-0.5SH_1x12-1MP_P0.50mm_Horizontal; MPN AFC01-S12FCA-00; LCSC C262661

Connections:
+3V3: J1.5; also elsewhere on the board
DISP_BOOT: J1.11; also elsewhere on the board
DISP_IRQ: J1.9; also elsewhere on the board
DISP_NRST: J1.10; also elsewhere on the board
GND: C7.2, J1.3, J1.4, J1.12; also elsewhere on the board
SPI_CS: J1.8; also elsewhere on the board
SPI_MOSI: J1.7; also elsewhere on the board
SPI_SCLK: J1.6; also elsewhere on the board
VSYS: C7.1, J1.1, J1.2; also elsewhere on the board

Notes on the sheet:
UNIFIED DISPLAY-MODULE CONNECTOR - J1 AFC01-S12FCA-00 (LCSC C262661) 0.5mm 12-pos FFC to the MCU board. SAME connector + pinout as the RGB- matrix board's J1 and mcu J3 -> the display modules are INTERCHANGEABLE. PIN SIGNAL PIN SIGNAL 1 VSYS 7 SPI_MOSI 2 VSYS 8 SPI_CS 3 GND 9 DISP_IRQ 4 GND 10 DISP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

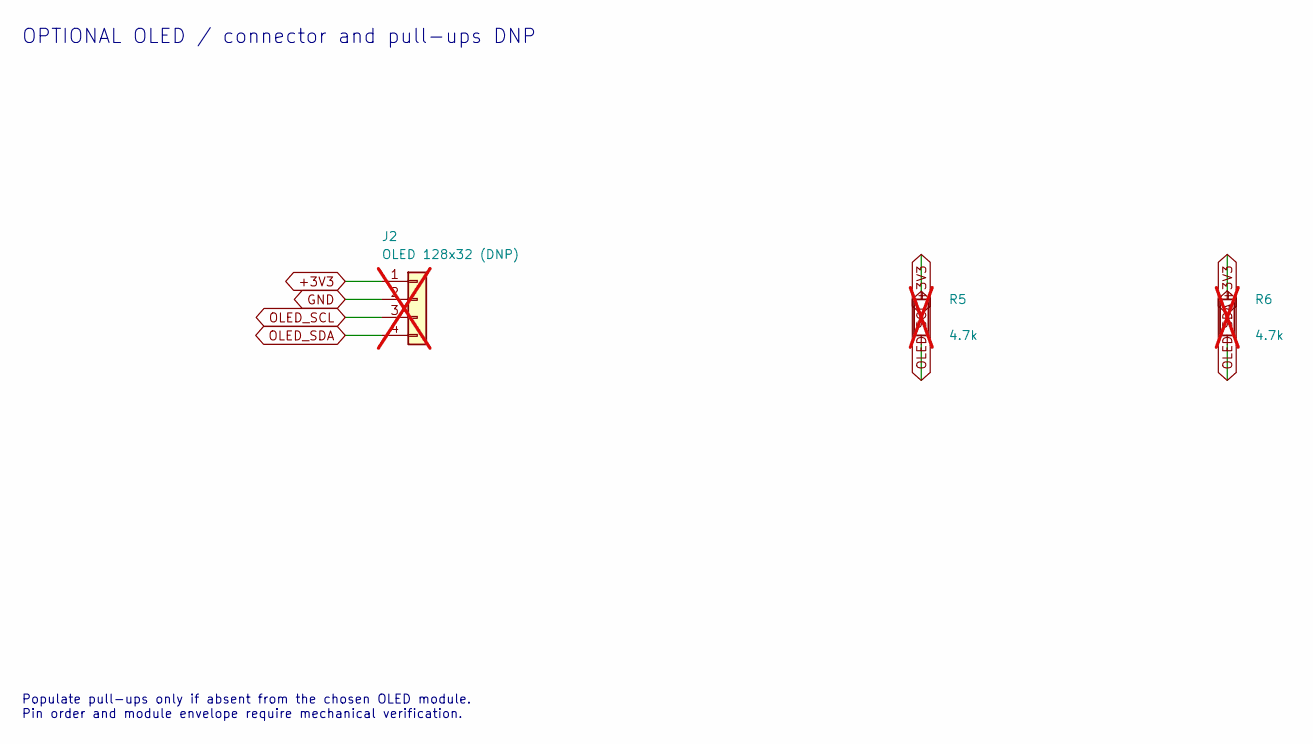
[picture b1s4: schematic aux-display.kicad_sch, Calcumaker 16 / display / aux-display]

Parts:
J2: OLED 128x32 (DNP); PinHeader_1x04_P2.54mm_Vertical; MPN PZ254V-11-04P; LCSC C2691448; not fitted
R5, R6: 4.7k; R_0402_1005Metric; not fitted

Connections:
+3V3: J2.1, R5.1, R6.1; also elsewhere on the board
GND: J2.2; also elsewhere on the board
OLED_SCL: J2.3, R5.2; also elsewhere on the board
OLED_SDA: J2.4, R6.2; also elsewhere on the board

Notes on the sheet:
Populate pull-ups only if absent from the chosen OLED module. Pin order and module envelope require mechanical verification.
OPTIONAL OLED / connector and pull-ups DNP

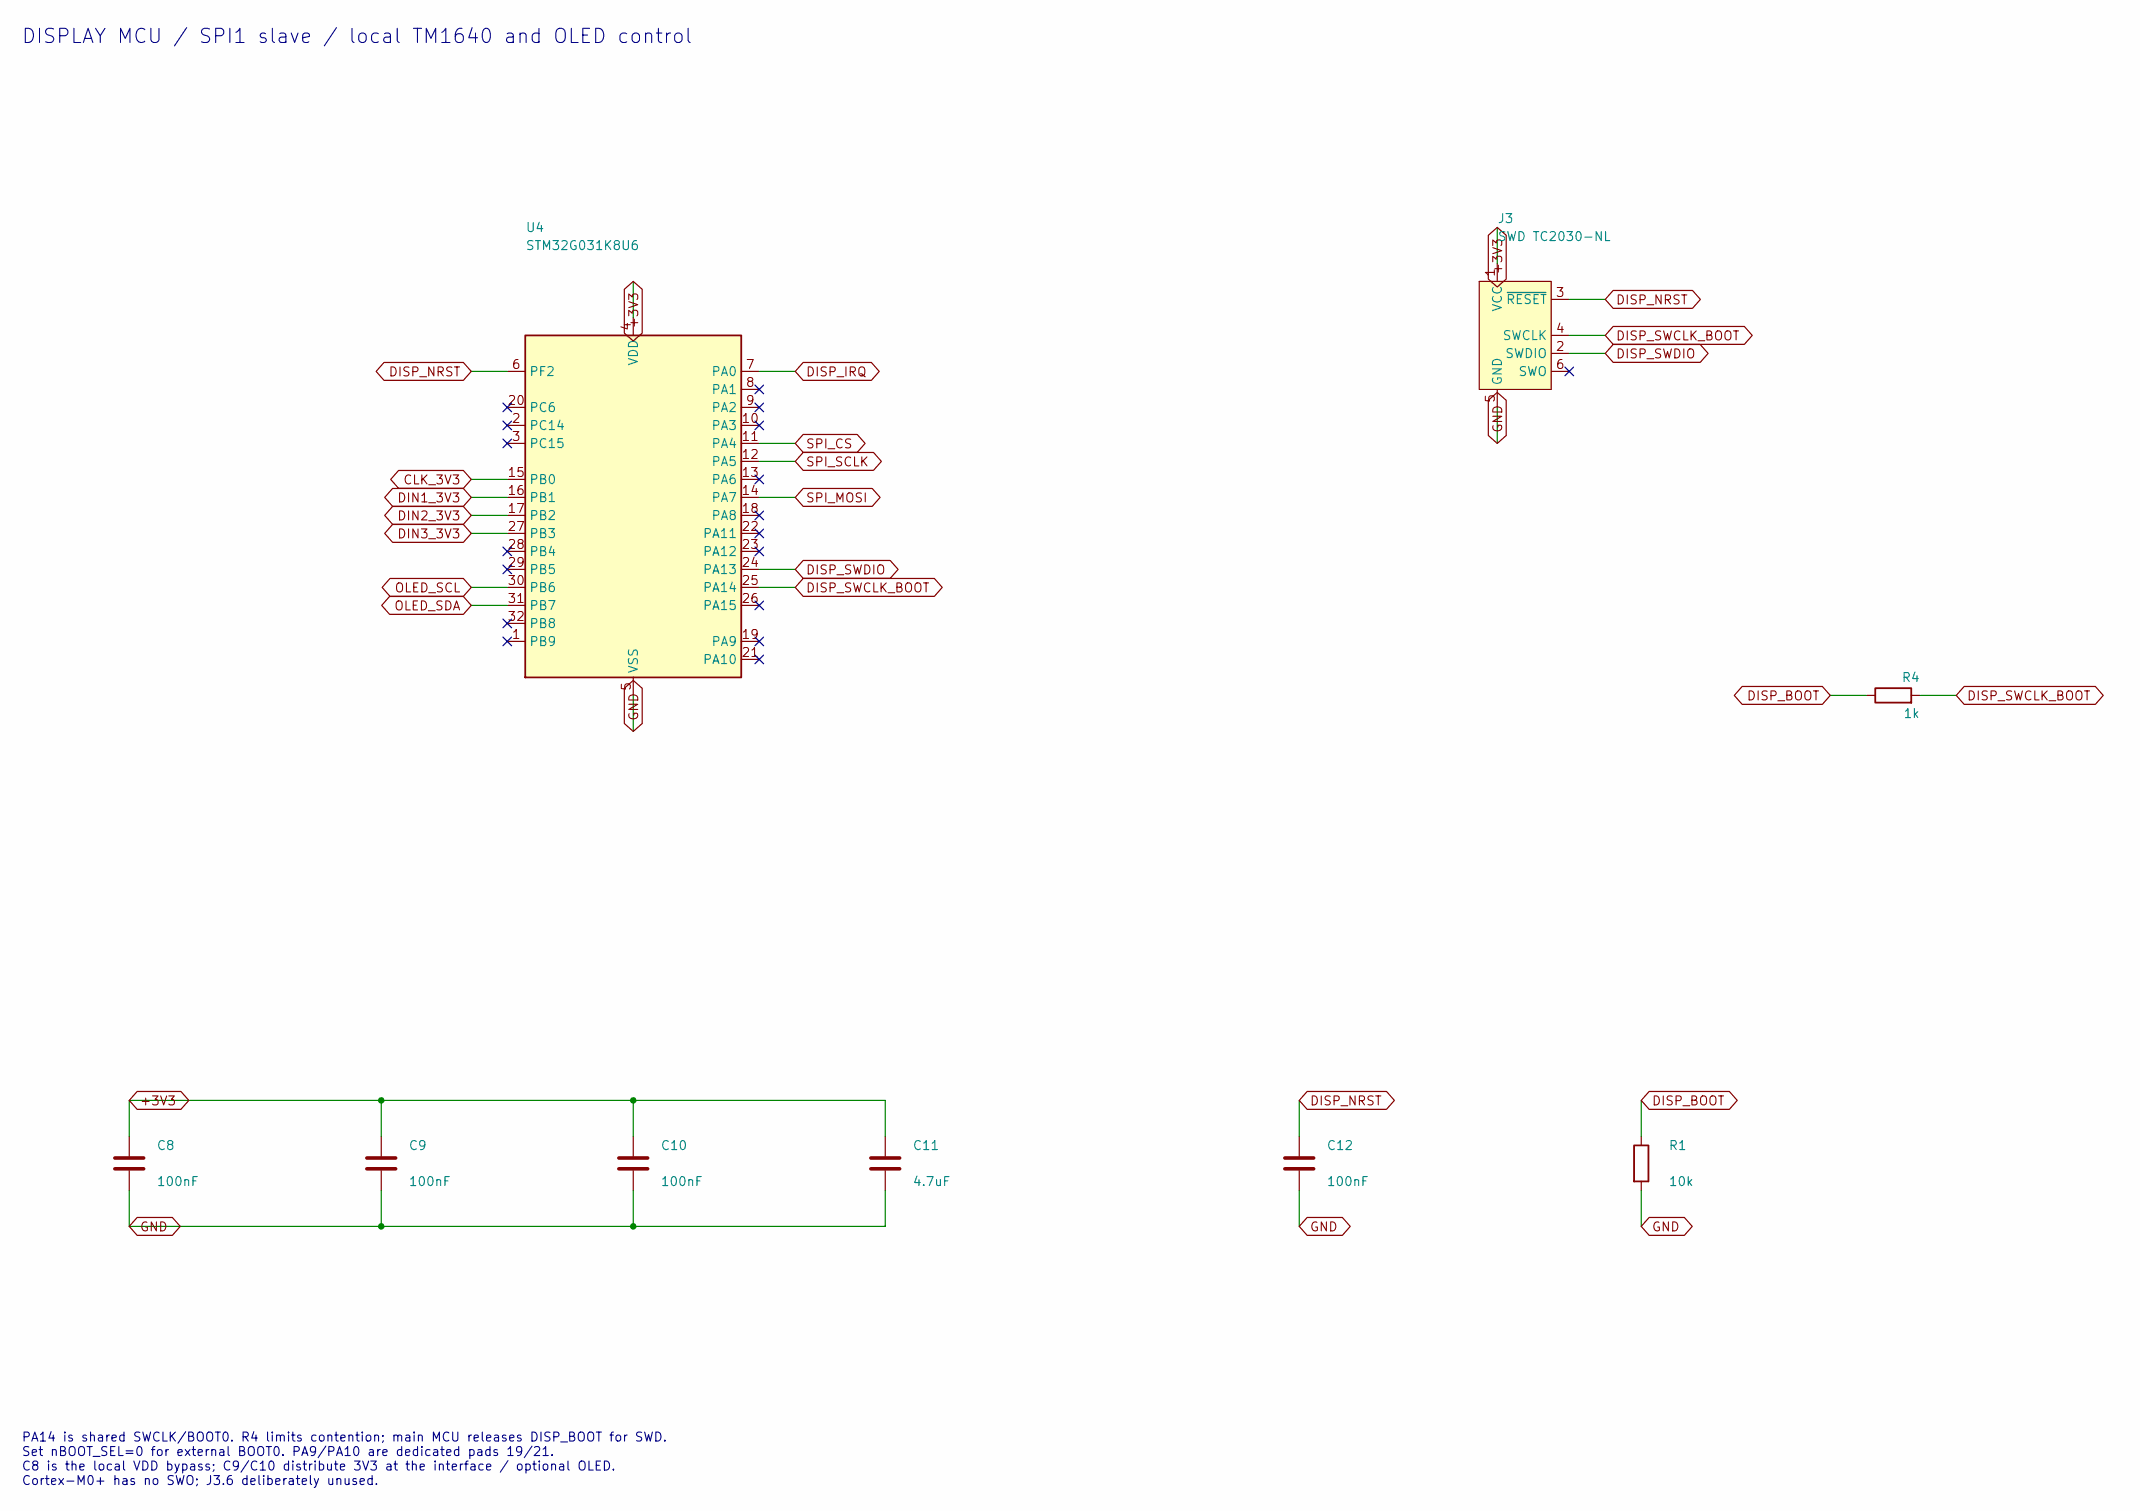
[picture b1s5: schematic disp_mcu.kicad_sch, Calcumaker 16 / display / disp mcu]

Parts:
C8, C9, C10, C12: 100nF; C_0402_1005Metric; LCSC C1525
C11: 4.7uF; C_0603_1608Metric; LCSC C23630
J3: SWD TC2030-NL; Tag-Connect_TC2030-IDC-NL_2x03_P1.27mm_Vertical
R1: 10k; R_0402_1005Metric; LCSC C25744
R4: 1k; R_0402_1005Metric
U4: STM32G031K8U6; UFQFPN-32-1EP_5x5mm_P0.5mm_EP3.5x3.5mm; MPN STM32G031K8U6; LCSC C432207

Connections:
+3V3: C8.1, C9.1, C10.1, C11.1, J3.1 (VCC), U4.4 (VDD); also elsewhere on the board
CLK_3V3: U4.15 (PB0); also elsewhere on the board
DIN1_3V3: U4.16 (PB1); also elsewhere on the board
DIN2_3V3: U4.17 (PB2); also elsewhere on the board
DIN3_3V3: U4.27 (PB3); also elsewhere on the board
DISP_BOOT: R1.1, R4.1; also elsewhere on the board
DISP_IRQ: U4.7 (PA0); also elsewhere on the board
DISP_NRST: C12.1, J3.3 (~RESET), U4.6 (PF2); also elsewhere on the board
DISP_SWCLK_BOOT: J3.4 (SWCLK), R4.2, U4.25 (PA14)
DISP_SWDIO: J3.2 (SWDIO), U4.24 (PA13)
GND: C8.2, C9.2, C10.2, C11.2, C12.2, J3.5 (GND), R1.2, U4.5 (VSS), U4.33 (VSS); also elsewhere on the board
OLED_SCL: U4.30 (PB6); also elsewhere on the board
OLED_SDA: U4.31 (PB7); also elsewhere on the board
SPI_CS: U4.11 (PA4); also elsewhere on the board
SPI_MOSI: U4.14 (PA7); also elsewhere on the board
SPI_SCLK: U4.12 (PA5); also elsewhere on the board

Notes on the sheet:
DISPLAY MCU / SPI1 slave / local TM1640 and OLED control
PA14 is shared SWCLK/BOOT0. R4 limits contention; main MCU releases DISP_BOOT for SWD. Set nBOOT_SEL=0 for external BOOT0. PA9/PA10 are dedicated pads 19/21. C8 is the local VDD bypass; C9/C10 distribute 3V3 at the interface / optional OLED. Cortex-M0+ has no SWO; J3.6 deliberately unused.
